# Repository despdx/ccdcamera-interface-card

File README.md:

CCD Camera Interface Card
======

Motivation
--------------
In order to run our CCD camera with our new Archon controller, in is necessary
to design and build an interface card/board to properly route electrical
connections from the Archon ERF8 connectors to the CCD personality card.  This
is the documentation for that card.

### Copyright 2016 Paul R. DeStefano
>   This program is free software: you can redistribute it and/or modify
>   it under the terms of the GNU General Public License as published by
>   the Free Software Foundation, either version 3 of the License, or
>   (at your option) any later version.

>   This program is distributed in the hope that it will be useful,
>   but WITHOUT ANY WARRANTY; without even the implied warranty of
>   MERCHANTABILITY or FITNESS FOR A PARTICULAR PURPOSE.  See the
>   GNU General Public License for more details.

>   You should have received a copy of the GNU General Public License
>   along with this program.  If not, see <http://www.gnu.org/licenses/>.

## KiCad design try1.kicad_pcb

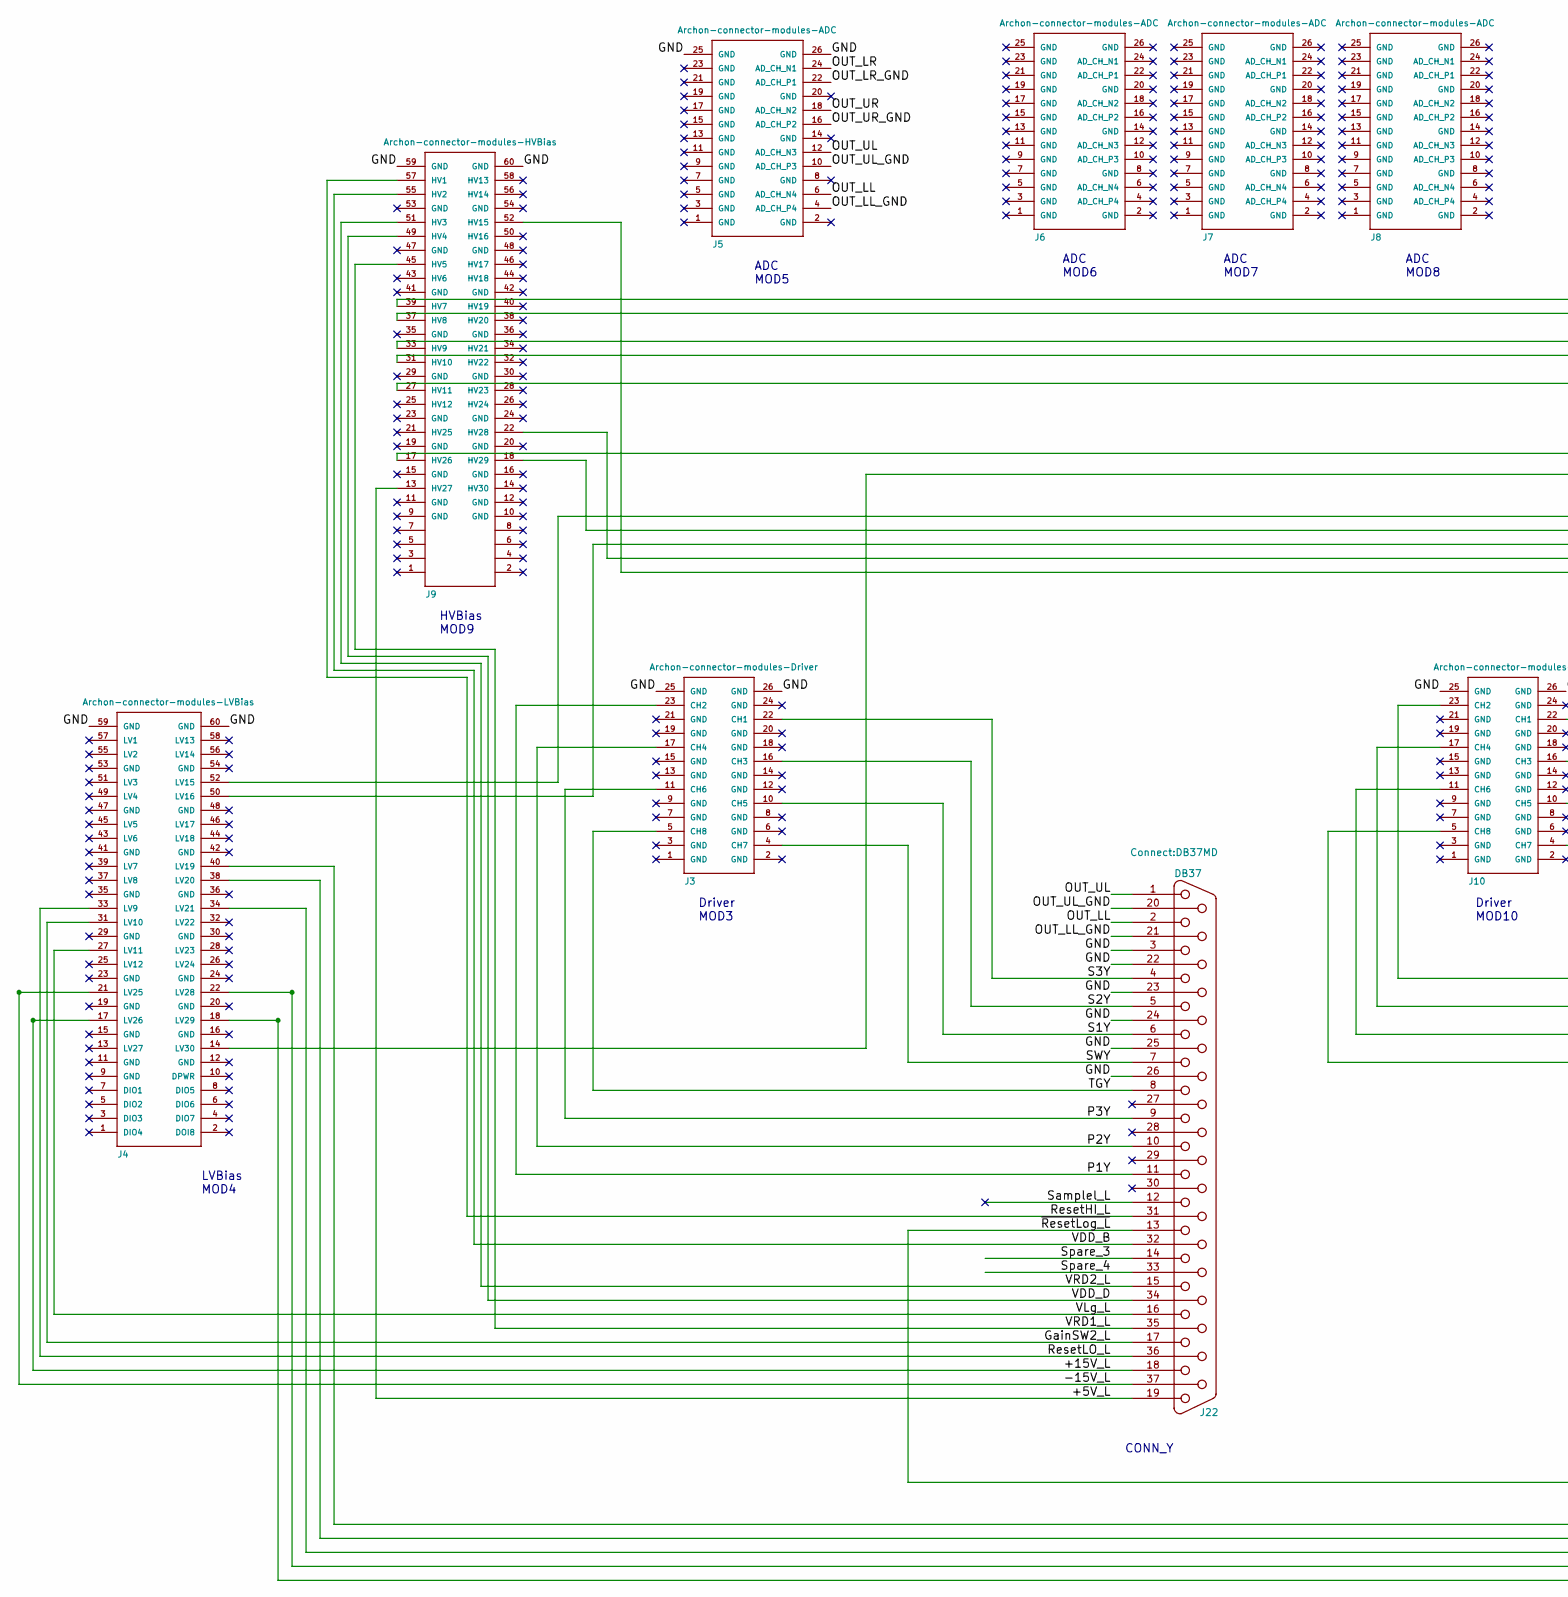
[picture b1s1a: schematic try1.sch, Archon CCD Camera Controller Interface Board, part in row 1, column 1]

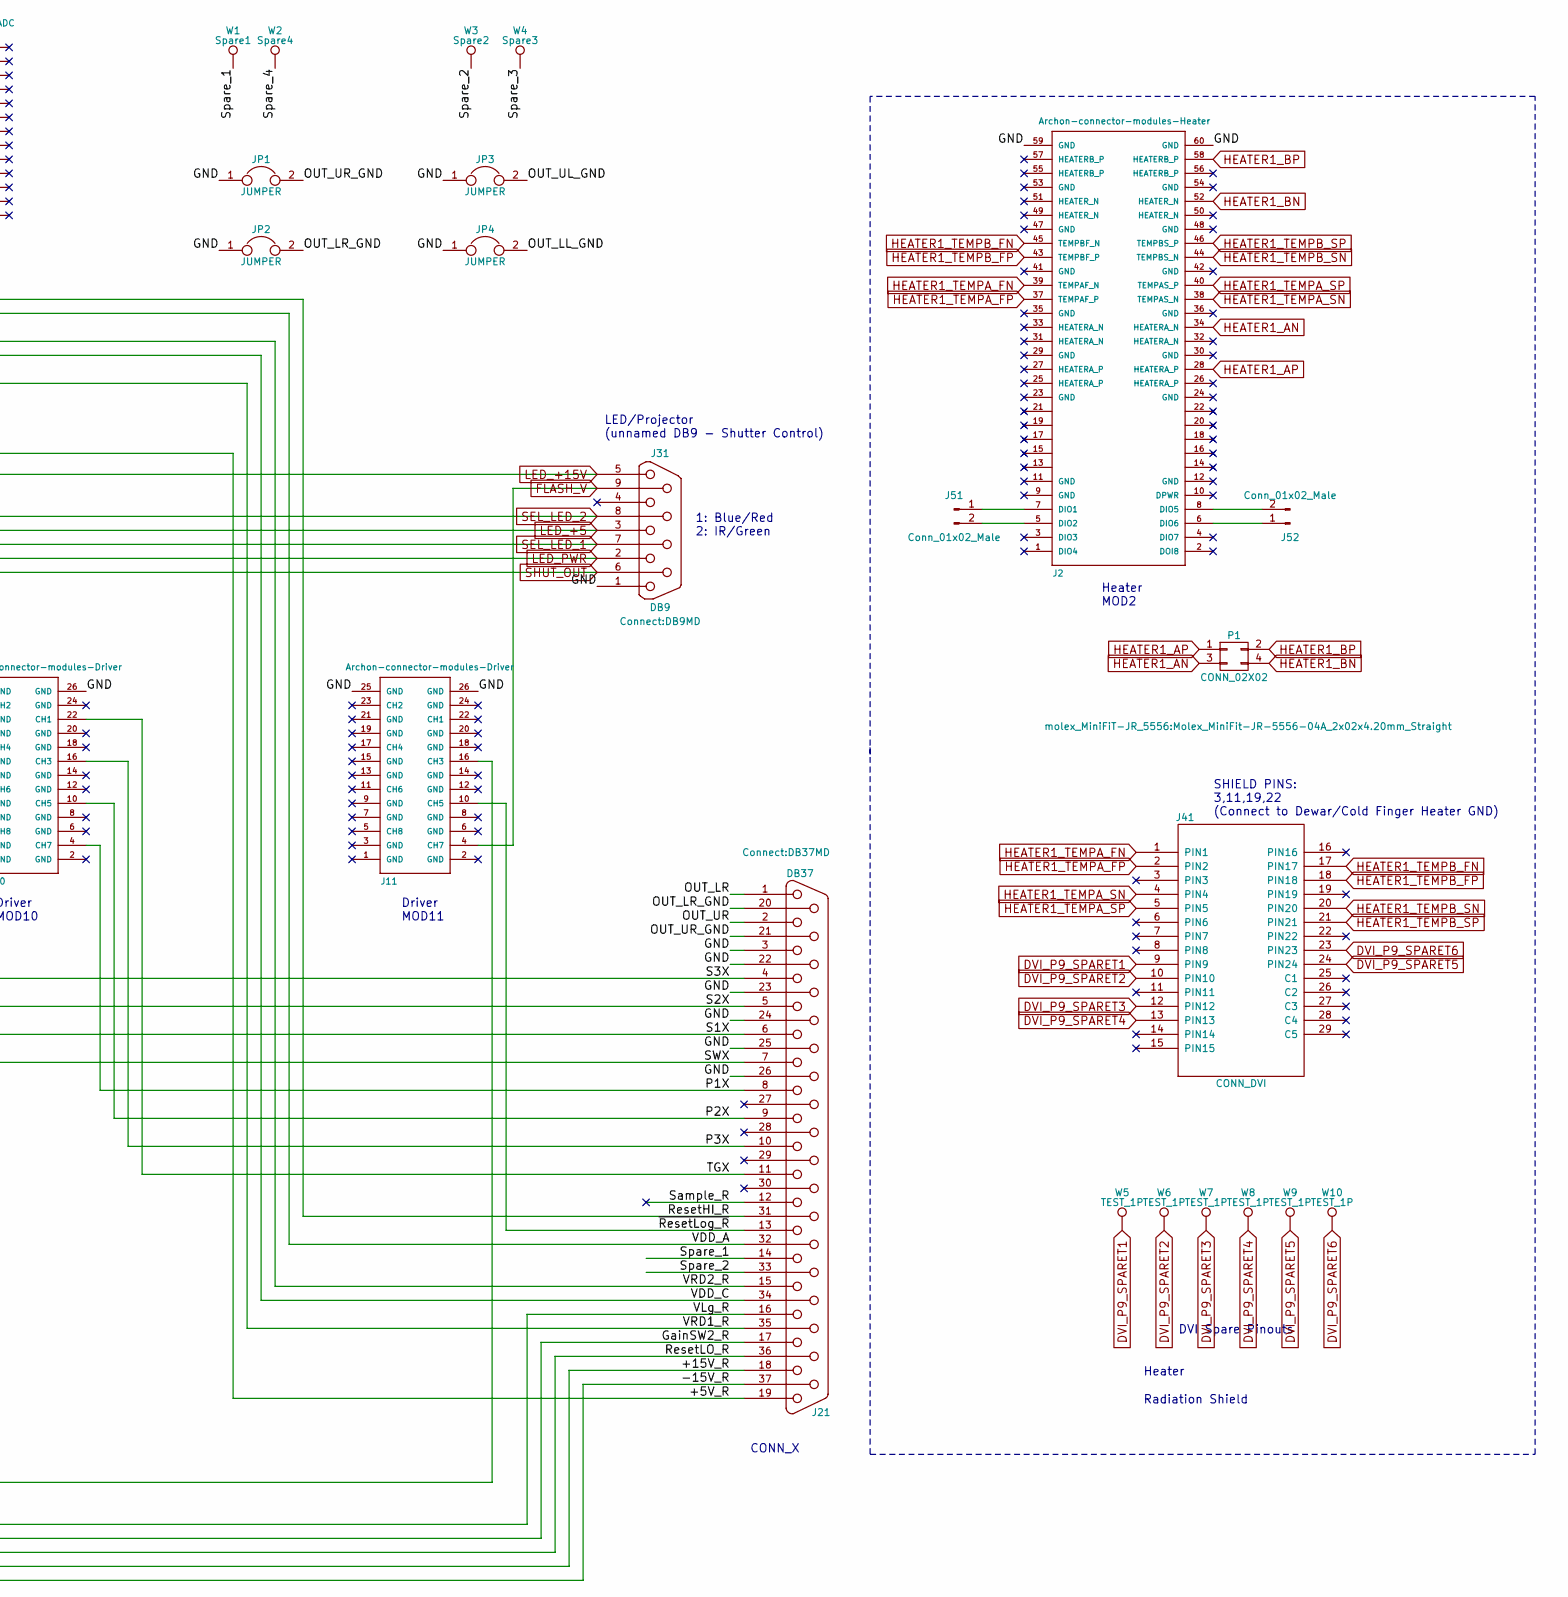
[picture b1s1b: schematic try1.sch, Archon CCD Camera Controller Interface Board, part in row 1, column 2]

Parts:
J2: Archon-connector-modules-Heater; ERM8-0030-XX.X-X-DV
J3, J10, J11: Archon-connector-modules-Driver; ERM8-013-XX.X-X-DV
J4: Archon-connector-modules-LVBias; ERM8-0030-XX.X-X-DV
J5, J6, J7, J8: Archon-connector-modules-ADC; ERM8-013-XX.X-X-DV
J9: Archon-connector-modules-HVBias; ERM8-0030-XX.X-X-DV
J21, J22: DB37; DB37MD
J31: DB9; DB9MD
J41: CONN_DVI; MOLEX_DVI_29pin_PN743203000
J51, J52: Conn_01x02_Male; Pin_Header_Straight_1x02_Pitch2.54mm
JP1, JP2, JP3, JP4: JUMPER; Pin_Header_Straight_1x02
P1: CONN_02X02; Molex_MiniFit-JR-5556-04A_2x02x4.20mm_Straight
W1: Spare1; SolderWirePad_single_1-5mmDrill
W2: Spare4; SolderWirePad_single_1-5mmDrill
W3: Spare2; SolderWirePad_single_1-5mmDrill
W4: Spare3; SolderWirePad_single_1-5mmDrill
W5, W6, W7, W8, W9, W10: TEST_1P; Pin_Header_Straight_1x01

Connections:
/+5V_L: J9.13 (HV27), J22.19
/+5V_R: J9.17 (HV26), J21.19
/+15V_L: J4.17 (LV26), J22.18
/+15V_R: J4.22 (LV28), J21.18
/-15V_L: J4.21 (LV25), J22.37
/-15V_R: J4.18 (LV29), J21.37
/GND: J2.59 (GND), J2.60 (GND), J3.25 (GND), J3.26 (GND), J4.59 (GND), J4.60 (GND), J5.25 (GND), J5.26 (GND), J9.59 (GND), J9.60 (GND), J10.25 (GND), J10.26 (GND), J11.25 (GND), J11.26 (GND), J21.3, J21.22, J21.23, J21.24, J21.25, J21.26, J22.3, J22.22, J22.23, J22.24, J22.25, J22.26, J31.1, JP1.1, JP2.1, JP3.1, JP4.1
/GainSW2_L: J4.31 (LV10), J22.17
/GainSW2_R: J4.38 (LV20), J21.17
/OUT_LL: J5.6 (AD_CH_N4), J22.2
/OUT_LL_GND: J5.4 (AD_CH_P4), J22.21, JP4.2
/OUT_LR: J5.24 (AD_CH_N1), J21.1
/OUT_LR_GND: J5.22 (AD_CH_P1), J21.20, JP2.2
/OUT_UL: J5.12 (AD_CH_N3), J22.1
/OUT_UL_GND: J5.10 (AD_CH_P3), J22.20, JP3.2
/OUT_UR: J5.18 (AD_CH_N2), J21.2
/OUT_UR_GND: J5.16 (AD_CH_P2), J21.21, JP1.2
/P1X: J10.4 (CH7), J21.8
/P1Y: J3.23 (CH2), J22.11
/P2X: J10.10 (CH5), J21.9
/P2Y: J3.17 (CH4), J22.10
/P3X: J10.16 (CH3), J21.10
/P3Y: J3.11 (CH6), J22.9
/ResetHI_L: J9.57 (HV1), J22.31
/ResetHI_R: J9.39 (HV7), J21.31
/ResetLO_L: J4.33 (LV9), J22.36
/ResetLO_R: J4.34 (LV21), J21.36
/S1X: J10.11 (CH6), J21.6
/S1Y: J3.10 (CH5), J22.6
/S2X: J10.17 (CH4), J21.5
/S2Y: J3.16 (CH3), J22.5
/S3X: J10.23 (CH2), J21.4
/S3Y: J3.22 (CH1), J22.4
/SWX: J10.5 (CH8), J21.7
/SWY: J3.4 (CH7), J22.7
/Sample_R: J21.12
/Samplel_L: J22.12
/Spare_1: J21.14, W1.1
/Spare_2: J21.33, W3.1
/Spare_3: J22.14, W4.1
/Spare_4: J22.33, W2.1
/TGX: J10.22 (CH1), J21.11
/TGY: J3.5 (CH8), J22.8
/VDD_A: J9.37 (HV8), J21.32
/VDD_B: J9.55 (HV2), J22.32
/VDD_C: J9.31 (HV10), J21.34
/VDD_D: J9.49 (HV4), J22.34
/VLg_L: J4.27 (LV11), J22.16
/VLg_R: J4.40 (LV19), J21.16
/VRD1_L: J9.45 (HV5), J22.35
/VRD1_R: J9.27 (HV11), J21.35
/VRD2_L: J9.51 (HV3), J22.15
/VRD2_R: J9.33 (HV9), J21.15
/~ResetLog_L: J11.16 (CH3), J22.13
/~ResetLog_R: J11.10 (CH5), J21.13
DVI_P9_SPARET1: J41.9 (PIN9), W5.1
DVI_P9_SPARET2: J41.10 (PIN10), W6.1
DVI_P9_SPARET3: J41.12 (PIN12), W7.1
DVI_P9_SPARET4: J41.13 (PIN13), W8.1
DVI_P9_SPARET5: J41.24 (PIN24), W9.1
DVI_P9_SPARET6: J41.23 (PIN23), W10.1
FLASH_V: J11.4 (CH7), J31.9
HEATER1_AN: J2.34 (HEATERA_N), P1.3
HEATER1_AP: J2.28 (HEATERA_P), P1.1
HEATER1_BN: J2.52 (HEATER_N), P1.4
HEATER1_BP: J2.58 (HEATERB_P), P1.2
HEATER1_TEMPA_FN: J2.39 (TEMPAF_N), J41.1 (PIN1)
HEATER1_TEMPA_FP: J2.37 (TEMPAF_P), J41.2 (PIN2)
HEATER1_TEMPA_SN: J2.38 (TEMPAS_N), J41.4 (PIN4)
HEATER1_TEMPA_SP: J2.40 (TEMPAS_P), J41.5 (PIN5)
HEATER1_TEMPB_FN: J2.45 (TEMPBF_N), J41.17 (PIN17)
HEATER1_TEMPB_FP: J2.43 (TEMPBF_P), J41.18 (PIN18)
HEATER1_TEMPB_SN: J2.44 (TEMPBS_N), J41.20 (PIN20)
HEATER1_TEMPB_SP: J2.46 (TEMPBS_P), J41.21 (PIN21)
LED_+5: J9.18 (HV29), J31.3
LED_+15V: J4.14 (LV30), J31.5
LED_PWR: J9.22 (HV28), J31.2
unnamed: J2.5 (DIO2), J51.2
unnamed: J2.6 (DIO6), J52.1
unnamed: J2.7 (DIO1), J51.1
unnamed: J2.8 (DIO5), J52.2
SEL_LED_1: J4.50 (LV16), J31.7
SEL_LED_2: J4.52 (LV15), J31.8
SHUT_OUT: J9.52 (HV15), J31.6

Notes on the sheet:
Heater MOD2
Driver MOD3
LVBias MOD4
ADC MOD5
ADC MOD6
ADC MOD7
ADC MOD8
HVBias MOD9
Driver MOD10
Driver MOD11
CONN_Y
CONN_X
LED/Projector (unnamed DB9 - Shutter Control)
Heater
Radiation Shield
SHIELD PINS: 3,11,19,22 (Connect to Dewar/Cold Finger Heater GND)
1: Blue/Red 2: IR/Green
DVI Spare Pinouts

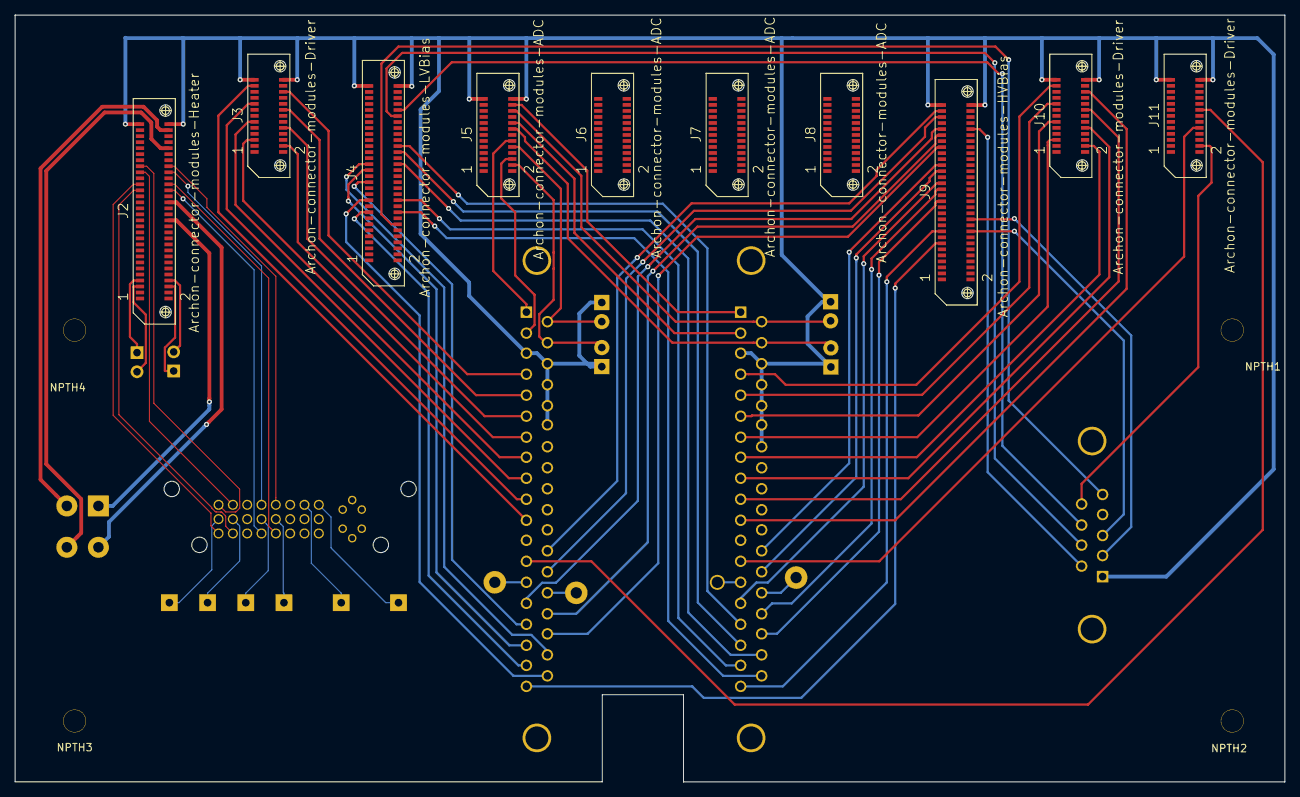
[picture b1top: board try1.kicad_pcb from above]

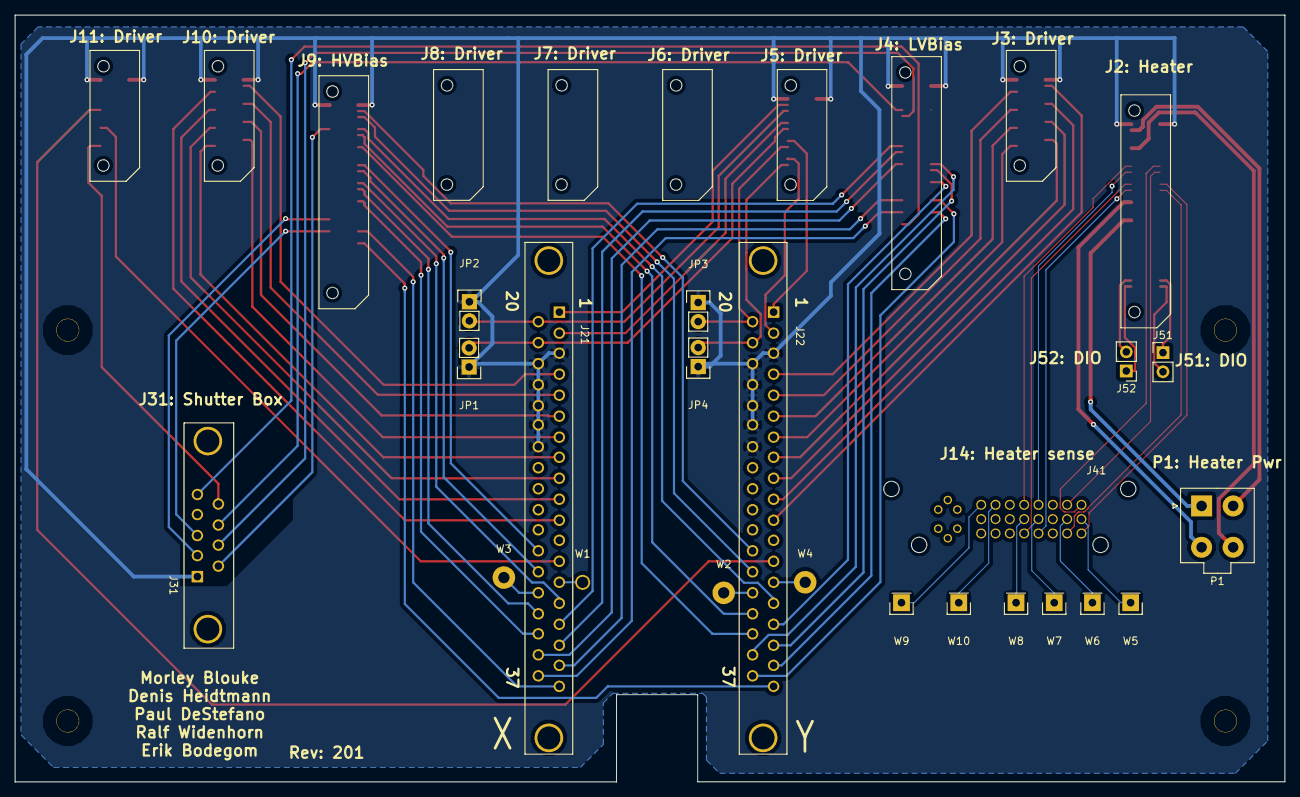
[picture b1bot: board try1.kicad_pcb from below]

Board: 2 copper layers, 168.9 x 102.0 mm, 35 parts (21 on the bottom side), 82 nets.

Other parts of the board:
NPTH1, NPTH2, NPTH3, NPTH4: archonInterfaceMountingHole

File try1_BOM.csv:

Source,/home/pdestefa/tmp/ccdProject/testPCBdesign/try1.sch
Kicad Rev,Eeschema 4.0.3-1.fc24-product
Generated Date,Tue 13 Sep 2016 11:20:06 PM PDT

Title,Archon CCD Camera Controller Interface Board
Company,Porltand State University
Revision,41
Date Issue,2016-07-08
Comment,Copyright 2016 Paul R. DeStefano

Reference,Value,Library,Library Ref
J22,DB37,conn,DB37
J21,DB37,conn,DB37
J2,Archon-connector-modules-Heater,archon,Archon-connector-modules-Heater
J3,Archon-connector-modules-Driver,archon,Archon-connector-modules-Driver
J4,Archon-connector-modules-LVBias,archon,Archon-connector-modules-LVBias
J5,Archon-connector-modules-ADC,archon,Archon-connector-modules-ADC
J6,Archon-connector-modules-ADC,archon,Archon-connector-modules-ADC
J7,Archon-connector-modules-ADC,archon,Archon-connector-modules-ADC
J8,Archon-connector-modules-ADC,archon,Archon-connector-modules-ADC
J9,Archon-connector-modules-HVBias,archon,Archon-connector-modules-HVBias
J10,Archon-connector-modules-Driver,archon,Archon-connector-modules-Driver
J11,Archon-connector-modules-Driver,archon,Archon-connector-modules-Driver
J31,DB9,conn,DB9
J41,CONN_DVI,try1-cache,CONN_DVI
P1,CONN_02X02,conn,CONN_02X02
W5,TEST_1P,conn,TEST_1P
W6,TEST_1P,conn,TEST_1P
W7,TEST_1P,conn,TEST_1P
W8,TEST_1P,conn,TEST_1P
W9,TEST_1P,conn,TEST_1P
W10,TEST_1P,conn,TEST_1P
W1,Spare1,conn,TEST_1P
W2,Spare4,conn,TEST_1P
W4,Spare3,conn,TEST_1P
W3,Spare2,conn,TEST_1P
JP1,JUMPER,device,JUMPER
JP2,JUMPER,device,JUMPER
JP3,JUMPER,device,JUMPER
JP4,JUMPER,device,JUMPER

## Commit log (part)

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2016-07-12 Initial Commit v4
2016-07-20 Version 7
2016-07-20 Version 11
    Big jump. I got proper part libraries (.lib) for KiCad by using a ULP
    for Eagle to convert Eagle part libraries (.lbr) to KiCad format.
2016-07-21 Rename connectors, conflicts
2016-07-21 Version 12
2016-07-21 archon.lib update: narrow symbols for LV/HVbias
2016-07-21 Remake schematic from project archon libarary
    I replaced all of the ERM8 symbols with the project's archon library
    that I just made.
2016-07-22 Label dewar connections
2016-07-22 Add true no-connect flag to Archon pins
    Some pins behind the Archon ERF8 connectors are, in fact, not connected
    to anything on their Archon modules. I marked these on the schematic.
    Maybe I should mark them on in the archon part library?
2016-07-22 Add additional connectors
    Added two RJ45 connectors for heater.
    Add DB9 for projector and LED control.
2016-07-22 Change position of RJ45 connectors
2016-07-22 Version 31
2016-07-29 Finish version 31
2016-08-03 Version 41: Partial Wiring
    Still very incomplete, but I finished the first pass on wiring. This
    version includes Morley's first pin assignments and some extra changes
    we talked about, today.
2016-08-18 Connect heater/DVI, label shutter connector
2016-08-23 schematic: chg ResetHI_L/R to ~(not) logic
2016-08-23 Update comment for DVI connector re:shield pins
2016-08-23 Rename GND pin on Shutter Connector
2016-08-23 Update Dewar PINs
    Changed GND to connector-specific names.
    Connect 5V,15V,&-15V to bias modules.
    Change GainSW2 name to connector-specific names.
2016-08-25 Connect signal ground, add LED select jumper
    Add hack to connect CCD signal ground to Driver module
    Add jumper component for selection of LED in dewar, no yet connected
    Added some text comments
    Reposition Heater module
2016-08-25 Fix DVI spare pin label names
2016-08-31 Change +-15V to LV low current biases
    I previously connected +-15 to HV biases, but we need high current, for
    one thing, and we also rather use LV, eventhought it only allows +-14V.
2016-08-31 Reassign LV4 CH3&4 to GainSW2;CH4&5 to 5V
    I moved LV4 low current channels 3&4 to GainSW2 on the dewar connectors.
    5V only needs low current, so I assigned those to LV biases 5&6, which
    were freed in the previous commit. In doing this, I reordered 5 & 15V
    connetions on the dewar.
2016-08-31 Conn LED Select to LV; Add CCD OUT jumpers to GND
    For now, I have connected the LED Select signals to LV biases as I know
    how to operate them, already. If I can use DIO, I'll change it.
    Added jumpers to connect CCD OUT_X_GND to interface GND plane. We're
    not sure at this point if this will help or hurt noise performance.
2016-09-01 Fix Shutter Control DB9 Pin Assignments
    Oops, I did this wrong. The illuminator/LED control board has J73, but
    it is a single row 10pin. The DB-9 is un-named on the schematic, but is
    documented. Denis found it and this patch corrects the pinouts.
2016-09-02 Finish Shutter
    Place biases and drivers for shutter control connection. This includes
    drivers for the FLASH_V/STB lines as well as HV high current biases for
    the LED power lines.
2016-09-02 Update Shutter Control
    Now I'm not so sure about the last commit. This patch actually
    completes the assignment of all shutter control pins. I'm not sure it's
    right, but it is complete, now.
    I also changed FLASH_STB to a HV high current bias, as I think it is
    actually the current source for the LEDs. 15V and 5V lines are still HV
    high current also, eventhough I think only two high current supplies are
2016-09-06 Change Sutter Connector Labels for LED Pins
    These "SHUT_" biases are really for the LEDs. So, we changed those label
    names to be more apropos.
2016-09-06 Assign ResetLO to LV, not HV
    ResetLO needs to go negative, so we must assign it to the LV module, not
    the HV module.
2016-09-07 Fix High Current Bias for SHUT+15V
    Shutter +15V may need 475mA. Only the Low Voltage high current biases
    are capable of this (max 500mA); the HV high current biases are limited
    to 250mA. This patch fixes that, I think, by borrowing one of the LVHC
    biases previously assigned to the pre-amp 5V, and assigning it to the
    shutter +15V. In exchange, the two pre-amp 5V lines are assigned HVHC
    biases. This line doesn't need to be as clean as other lines to the
2016-09-07 Rename FLASH_STB to LED_PWR
2016-09-08 Fix Nonconnect Pins On Module 4
2016-09-13 Finish ERC
    Deleted all other unmatched labels as ERC didn't like it.
2016-09-13 Remove GND component
    Removed the GND power component. It was causing an ERC error and I don't
    think we strictly need it.
2016-09-13 Fix Archon Heater Electrical Types
    Didn't do it right the first time. I think this is better.
2016-09-15 Add samtec Project Footprint Library
2016-09-15 Try Footprint Association in Schmatic
    While most of the components on the schematic had footprints assigned,
    they were only names to be matched later, I think, not direct links to
    footprints in specific libraries. When I went to CvPcb, it complained
    bitterly about not being able to find the ccdcamera library, which I never
    put into git. Regardless, Windows and Linux will not agree on the
    location of these footprints and futher adjustment is probably necessary.
2016-09-15 Add New Libraries to KiCad FP-Lib-Table
2016-09-20 Chery-Picked Updates from lab42
2016-09-20 Update Lib Cache
2016-09-20 Fix DVI Connector Symbol
    My footprint doesn't have 30 pins, so it complained. I removed pin 30
    from the symbol. We'll see if this helps.
2016-09-20 First Layout
    Finally we have something. Now, the hard part is aligning these parts.
2016-09-20 Unknown Change to PCB
2016-09-21 PCB Layout Updates
    Moved all but the Archon connectors to the back side of the PCB.
    Added layer alignment marks.
    Organized test points and jumpers.
2016-09-22 Place ERF8 Archon Connectors
2016-09-22 Try Updating Spare Pad Sizes
    Changed a footprint from the schematic. Next, we'll see how it propogates
    that change through to the layout.
2016-09-22 Lock Everything
2016-09-23 Fix DVI Footprint (Again)
    I think I finally got it! Using the advice I got from OSH Park and
    IRC#kicad, I re-made all the pads and holes on the DVI footprint. Then,
    I used "change footprint" in the PCBnew editor to update it in the
    layout.
2016-09-27 Add Frist Board Edge and Mounting Holes
    These are suggestive, not final. We'll probably need to play with
    these more, but I wanted to try it.
    I also turned the DB9 connector to same some space.
2016-09-27 Set fp-lib-table back to Linux
2016-09-29 Update Samtec ERM8- Footprint NPTH W/ OshPark Tol.
    Added 2.5 mils to NTPH mechanical holes on Archon parts.
2016-09-29 Update PDCB: OshPark NTPH Tol. Change of ERM8-
    I updated the PCB layout components with the new ERM8 footprints I just
    updated for more tolerance.
2016-10-04 Rotate DVI Part and Move Test Pins
    This untangles ratsnest for DVI and test pins.
2016-10-11 First Route with FreeRouter
    This is the first completed FreeRouter autoroute.
2016-10-11 FreeRouter Files
2016-10-13 Place GND Plane Before Freeroute
2016-10-19 WIP: FreeRouter Fixes
    Fixed the heater power traces a little bit, manually. I think I see how
    this could work, now.
    Still TODO:
    Check and fix all ground connections
    Eliminate isolated fill areas
    Double check connetions
2016-10-19 Reassign All DRV Channels
    Firstly, the previous assignments were just wrong. But, in addition, I
    assigned them based on board layout, instead of logical order.
    Also, I changed the schematic to help me think about this process.
2016-10-19 Delete Old DRV Traces
    After updating the schematic and exporting the new netlist, I updated the
    PCB. I thought this would delete all the old traces, but I had to do some
    of that myself. In any case, I think this is ready for me to route the
    new assignments for the driver modules.
2016-10-19 After FreeRoute Of Only New DRV Connections
2016-10-19 After Full FreeRouter Autoroute
    This is what we get if I let FreeRouter run over the whole board, not just
    the new DRV connections.
2016-10-24 Add GND Plane on Back Side
2016-11-02 Move VIA From Under Heater Header
2016-11-02 Move VIAs From Under Driver Header
2016-11-02 Move VIAs From Under ADC Header
2016-11-02 Move VIAs From Under HVBias Header
2016-11-02 Move VIA From Under Driver 11 Header
2016-11-05 Unknown Update To Archon Component Library
2016-11-05 Unknown PCB Layout Update
2016-11-09 Misc Update: Component Library & Netlist
2016-11-09 WIP: Manual Route: Start Over
    I had to flip and rotate the DB37 connectors because, looking at
    the part diagrams, I think I had them the wrong way.
    Yep, had to redo the ADC tracks, again.
2016-11-14 Move X & Y Connectors In Schematic
    This is like the board order, although, I'm not supposed to care
    if they match.
2016-11-15 Route Driver 3, Shift DB37 Up, Reroute
2016-11-16 Move Schematic Around
2016-11-16 Reassign Driver Channels from DRV10 DRV11
2016-11-16 Temporary Route DRV10 &11
    This is just a first pass. I will have to clean these up later.
2016-11-16 Reassign LV4 Connections
2016-11-16 Reassign And Complete LV4 Connections
2016-11-16 Problem: Lost High Current Assignments
    While reassigning pins for the board layout, I forgot that some of
    bias modules had different low and high current channels. I've
    tried to recover that in this commit, but it may be wrong.
    Also, I changed the orientation of the DB9 header.
2016-11-17 Maybe Recovered
    Okay, it's not looking too bad. I reassigned the LVBias and HVBias
    high current pins and rerouted some of the LV traces. It looks like
    the rest will work out.
2016-11-21 Route LVBias to DB9
2016-11-21 WIP: Route HVBias
2016-11-23 Reposition Schematic On Page
2016-11-23 Resize Schematic Page
2016-11-23 Finish GND Route Around Right Perifery
2016-11-23 Finsh HVBias, Finish All Traces
    Wow, it's actually done. I still need to audit and fix up some ugly
    push/shove routing segments. But, all the connections are connected.
2016-11-23 Update Project File
2016-11-23 Resize Schematic Yet Again
2016-11-23 PCB Layout Fix-Ups
2016-12-07 Tweak Heater Traces
2016-12-07 Adjust Silks, Names
2016-12-07 More Hard GND Traces
2016-12-12 Fix DB37, Need Male Part, Not Female
2016-12-12 Update Project Timestamp
2016-12-12 Refill Zones
    I hope this will be the last refil. I still think I'll remove the
    front-side fill.
2016-12-12 Remove Front Side GND Plane
2017-02-22 Add Archon Opening Dimensions to Layout
2017-02-27 Place Chassis Dimensions
    The board was too big! Argh. I've started to redesign the whole
    thing by recalcuating the board size. To do this, I placed edges
    for the Archon Chassis around the board located by the placement
    holes of the ERM8 connectors.
    Next, I placed new edge cuts, including the notch that I'll need
    to work around for the new board design.
2017-11-06 WIP: Fix Board Size: Moved Footprints
    I have moved the DB37 footprints, and other, so that everything will
    fit into the proper board size.
    The board edge isn't working, correctly, however. I need to remake
    it to be continuous.
2017-11-07 Make Notch Wider
2017-11-13 Shave Five More mm Off Right Side
2017-11-13 Rebuild ADC Connections After Board Resizing
2017-12-12 Update Net List
2017-12-12 WIP Redo All Traces, Adjust Pads
    I'm redoing all the traces, now. I traced the first set of cross-
    board traces from HVbias on conn Y on the opposite side.
    I also adjusted the big pads to be smaller and closer to the connectors.
2017-12-12 WIP Retrace Everything
    I think this is working. I still have to adjust everything, but
    these connections are the rough paths I want.
2017-12-13 WIP Add Last Driver Traces
2017-12-13 Expose GPIO Pins
    I'm not sure this is exactly what we want, but the core is done. If we
    want to change the footprint for these pins or move them, it will be
    relatively easy, now that the connections have been made.
2017-12-13 More Fine Tuning
2017-12-13 Add Extra Ground Connection
2017-12-13 Add Keepout Area, Refill Ground Plane
2017-12-21 Add Extra Silks to Backside
    Added some annotation text to the backside in the silk layer.
2017-12-26 Update Schematic Export to PDF
2017-12-26 Fix Board NPTH For Mounting
2018-01-04 Minor Change to One Trace
2018-01-19 Add Revsion, Date, Rev Silk to Layout, Update Date on Schematic

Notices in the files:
try1.sch:
Copyright 2017 Paul R. DeStefano
